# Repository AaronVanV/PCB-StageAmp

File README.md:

# 2 Stage Amplifier

2 Stage Amplifier using BC847 transistors. All components should be SMD, except for pinheaders and connectors.

Name: Aaron Van Vyve

## Schematic

## PCB

| Front | Back |
|---|---|
|   |   |

## BOM

The BOM or Bill of Materials consists out of a list of all the components with some of theire properties. 

| Designator | Quantity | Description | Footprint | Farnell ordercode | Price |
|---|---|---|---|---|---|
| R1, R3, R5, R7 | 4 | 4k7 ohm | 0805 | [1750763](https://be.farnell.com/panasonic/erjp06f4701v/res-4k7-1-0-5w-0805-thick-film/dp/1750763) | 0.101 € (you get 10) | <!-- TODO: remove this example -->
| R2, R4 | 2 | 1k ohm | 0805 | [2861522](https://be.farnell.com/te-connectivity/crgcq0805f1k0/res-1k-1-0805-thick-film/dp/2861522) | 0.0371€ (you get 10) |
| R9 | 1 | 50 ohm | 0805|[2820487RL](https://be.farnell.com/vishay-foil-resistors/y402250r0000a9r/res-50r-0-05-0-2w-0805-metal-foil/dp/2820487RL)|13.18€ (you get 10) |
| Q1, Q2 | 2 | BC847 | 0805|[1081231](https://be.farnell.com/nexperia/bc847a-215/transistor-npn-sot-23/dp/1081231?st=bc847)|0.104€ (you get 5) |
| C1, C3 | 2 | 1uF | 0805|[1890109](https://be.farnell.com/wima/smdtc04100ta00kq00/cap-1-f-63v-10-pet-2824-smd/dp/1890109)|3.50€ |
| C2, C4 | 2 | 20uF | 0805|[C4AEGBU5200A12J](https://be.farnell.com/kemet/c4aegbu5200a12j/cap-20-f-450v-5-pp-radial/dp/2709775)|14.36€ |
| J1, J2 | 2 | Female 1x1 | |[2892466](https://be.farnell.com/amphenol-icc/68000-200hlf/connector-header-1pos-1row/dp/2892466)|0.21€ |
| Battery | 1 | 9V | 0805|[1018880](https://be.farnell.com/panasonic/6f22rel-1bp/battery-zinc-carbon-pp3/dp/1018880)|1.51€ |
Total price: 33.0021€

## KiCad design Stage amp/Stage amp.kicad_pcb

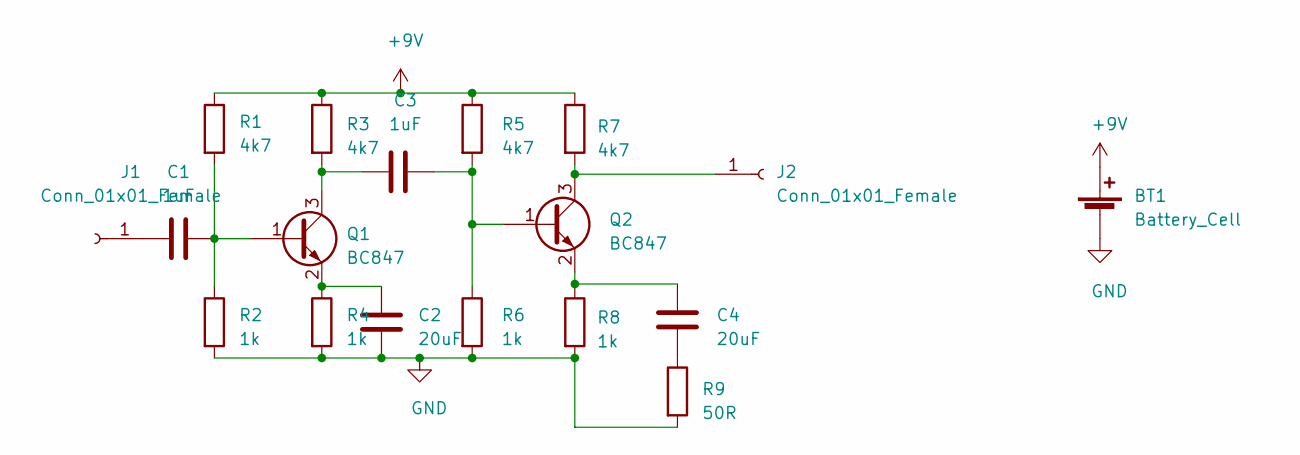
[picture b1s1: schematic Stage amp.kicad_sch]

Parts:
BT1: Battery_Cell; BatteryHolder_Keystone_103_1x20mm
C1, C3: 1uF; C_0805_2012Metric
C2, C4: 20uF; C_0805_2012Metric
J1, J2: Conn_01x01_Female; PinHeader_1x01_P2.54mm_Horizontal
Q1, Q2: BC847; SOT-23
R1, R3, R5, R7: 4k7; R_0805_2012Metric
R2, R4, R6, R8: 1k; R_0805_2012Metric
R9: 50R; R_0805_2012Metric

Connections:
+9V: BT1.1 (+), R1.1, R3.1, R5.1, R7.1
GND: BT1.2 (-), C2.1, R2.2, R4.2, R6.2, R8.2, R9.2
unnamed: C1.1, J1.1
unnamed: C1.2, Q1.1 (B), R1.2, R2.1
unnamed: C2.2, Q1.2 (E), R4.1
unnamed: C3.1, Q1.3 (C), R3.2
unnamed: C3.2, Q2.1 (B), R5.2, R6.1
unnamed: C4.1, R9.1
unnamed: C4.2, Q2.2 (E), R8.1
unnamed: J2.1, Q2.3 (C), R7.2

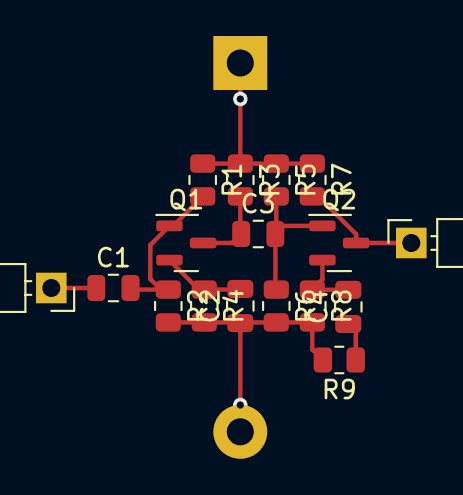
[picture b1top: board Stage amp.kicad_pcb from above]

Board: 2 copper layers, 18 parts (1 on the bottom side), 10 nets.

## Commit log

2021-02-28 to do BOM
